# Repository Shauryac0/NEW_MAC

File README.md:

# NEW_MAC
It is my first project, due to that I have made it simple.
This only took me more tha 5 days cause I recreated it 3 times.
The main purpose my macropad is to contro VLC:
 - Play/Pause
 - Volume Up
 - Volume Down
 - Mute
# PCB:
Shematics: 
PCB: 
(though I am thinking to wire the switches from RP2040 cause adding the switches is little difficult cause they are above the main PCB.
# CAD:

" />
# Firmware:
<> It is for VLC.
# BOM:
Things I have used are:
 - 4x SW_Push (Cherry MX)
 - XIAO-RP2040

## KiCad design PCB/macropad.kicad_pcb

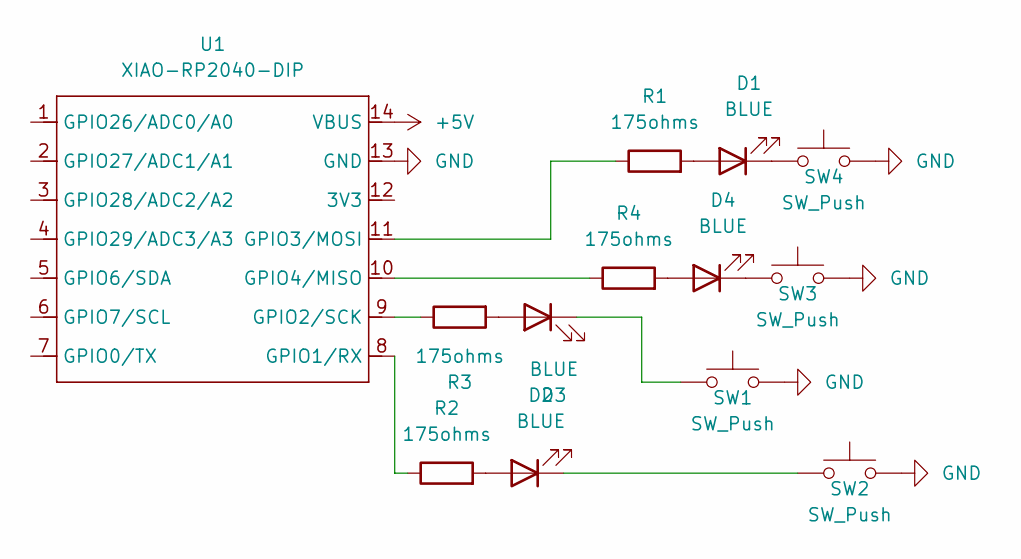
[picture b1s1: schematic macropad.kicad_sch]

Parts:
D1, D2, D3, D4: BLUE; LED_D5.0mm
R1, R2, R3, R4: 175ohms; R_0603_1608Metric
SW1, SW2, SW3, SW4: SW_Push; SW_Cherry_MX_1.00u_PCB
U1: XIAO-RP2040-DIP

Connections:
+5V: U1.14 (VBUS)
GND: SW1.2, SW2.2, SW3.2, SW4.2, U1.13 (GND)
unnamed: D1.2 (A), R1.2
unnamed: D1.1 (K), SW4.1
unnamed: D2.2 (A), R2.2
unnamed: D2.1 (K), SW2.1
unnamed: D3.2 (A), R3.2
unnamed: D3.1 (K), SW1.1
unnamed: D4.2 (A), R4.2
unnamed: D4.1 (K), SW3.1
unnamed: R2.1, U1.8 (GPIO1/RX)
unnamed: R3.1, U1.9 (GPIO2/SCK)
unnamed: R1.1, U1.11 (GPIO3/MOSI)
unnamed: R4.1, U1.10 (GPIO4/MISO)

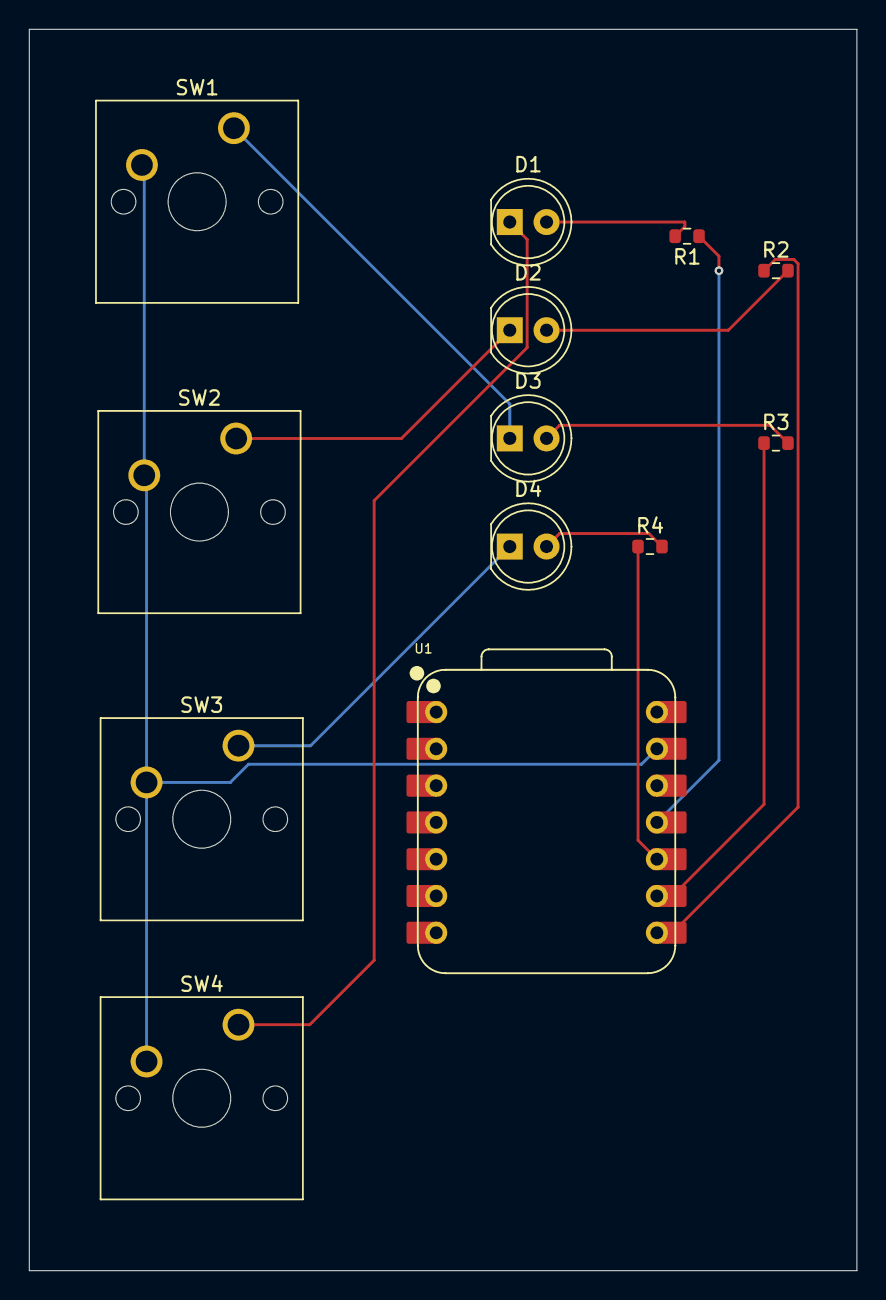
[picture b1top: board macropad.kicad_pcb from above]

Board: 2 copper layers, 57.2 x 85.7 mm, 13 parts (0 on the bottom side), 13 nets.

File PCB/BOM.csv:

"Reference","Qty","Value","DNP","Exclude from BOM","Exclude from Board","Footprint","Datasheet"
"D1,D2,D3,D4","4","BLUE","","","","LED_THT:LED_D5.0mm","~"
"R1,R2,R3,R4","4","175ohms","","","","Resistor_SMD:R_0603_1608Metric","~"
"SW1,SW2,SW3,SW4","4","SW_Push","","","","Button_Switch_Keyboard:SW_Cherry_MX_1.00u_PCB","~"
"U1","1","XIAO-RP2040-DIP","","","","Seeed Studio XIAO Series Library:XIAO-RP2040-DIP",""

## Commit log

2025-12-14 Create s
2025-12-14 Update README with project details and specifications
    Added project description, purpose, and details about PCB, CAD, firmware, and BOM.
2025-12-14 Add VLC macropad control script
    This script maps four buttons on a macropad to VLC media controls, allowing for play/pause, volume up, volume down, and mute functionality.
2025-12-17 Replace schematic and PCB images with new links
    Updated schematic and PCB images in README.
